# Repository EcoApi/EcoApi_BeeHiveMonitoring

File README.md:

# EcoApi Bee hive monitoring

description TBD

## Features

- External i2c sensor (ex: as6200, si7021, shtxx, ...)
- Microphone analog with max9814 (FFT with dma)
- Microphone i2s (FFT with dma)
- Weight with load scale using hx711 (opimized for 3.3V with noise filter), calibration by led information
- CPU STM32F411CEU6
- Motion detection using mercure tilt vibration sensor
- Internal i2c sensor (ex: bmp180, bme180, bme280, ...)
- Lora using rfm95w 
- Powered battery like : Li-ion, Li-po, 3xNimh, 4xNimh, LifePO4, Alkaline 3x1.5 / 2x1.5, Li-SOCL2, Li-Mn02, 18650
- Reverse battery protection
- USB charger
- Ultra low power in sleep mode (wakeup by external rtc) ~2µA
- Power in running mode TBD
- USB cdc from stm32
- Power switch for internal / external VCC (3.3V)
- Fram
- EEprom
- Flash SPI
- External nano watchdog
- Debug by led, Uart, 

## Hardware

### Characteristics

- Cpu
- Lora
- Consumption
- Fram
- EEprom
- Flash
- Rtc
- WDG
- HX711
- Protection battery
- Backup capacitor explanation
- Battery charger
- USB cdc
- Ldo
- Buck-boost
- Power Load switch
- Wakeup parts (button, wdg, motion, rtc)
- Dip switch
- Connector (load cell, external sensors, Battery, internal sensor, Debug & SWD)
- Push button
- Debug (Uart, USB CDC, SWD)
- ....

### Pcb

Front

Back

### Pinout

array of pins description

### pcb

describ options with 0R resistors. etc ...

#### JlcPcb production

- Bom and pick&place : https://support.jlcpcb.com/article/153-how-to-generate-bom-and-centroid-files-from-kicad-in-linux
- JlcPcb gerber files : https://support.jlcpcb.com/article/149-how-to-generate-gerber-and-drill-files-in-kicad

## Software

To be define (flow chart) ...

### Description

- Lora : ttn, webhook for beep, js decoder, frame format
- sensor template
- Sensors auto-detection
- Outside informations (temperature, pressure, humidity, wind, ...)
- Inside informations (Sound, temperature, humidity, gas, bee counter, custom sensor ...)
- System information (RSSI, VBATT, 
- describe directive in platforio.ini
- FFT on analog mic or I2S mic (parameters, range etc ...)
- sleep mode

### Ide & compilation

- pio
- plugins
- ....

### lmic debug ###

in platformio.ini

(1) uncomment :
	-D LMIC_DEBUG_LEVEL=2
	-D LMIC_ENABLE_event_logging=1
	-D LMIC_X_DEBUG_LEVEL=1

(2) replace in lmic/lmic.h :

#  ifdef LMIC_DEBUG_PRINTF_FN
#    define LMIC_X_DEBUG_PRINTF(f, ...) LMIC_DEBUG_PRINTF_FN(f, ## __VA_ARGS__)
#  else
#    error "LMIC_DEBUG_PRINTF_FN must be defined for LMIC_X_DEBUG_LEVEL > 0."
#  endif

by :

#define LMIC_X_DEBUG_PRINTF(f, ...) LMIC_DEBUG_PRINTF(f, ## __VA_ARGS__)

## how to

- Scale full or half
- Tare button
- Led information
- Motion tilt
- Debug
- usb charger leds
- Sleep on VBATT or 3.3V with slide switch
- Dip switch
- USB with android application (flutter.io or other)

## other 
[Editor.md](https://pandao.github.io/editor.md/en.html "Editor.md")

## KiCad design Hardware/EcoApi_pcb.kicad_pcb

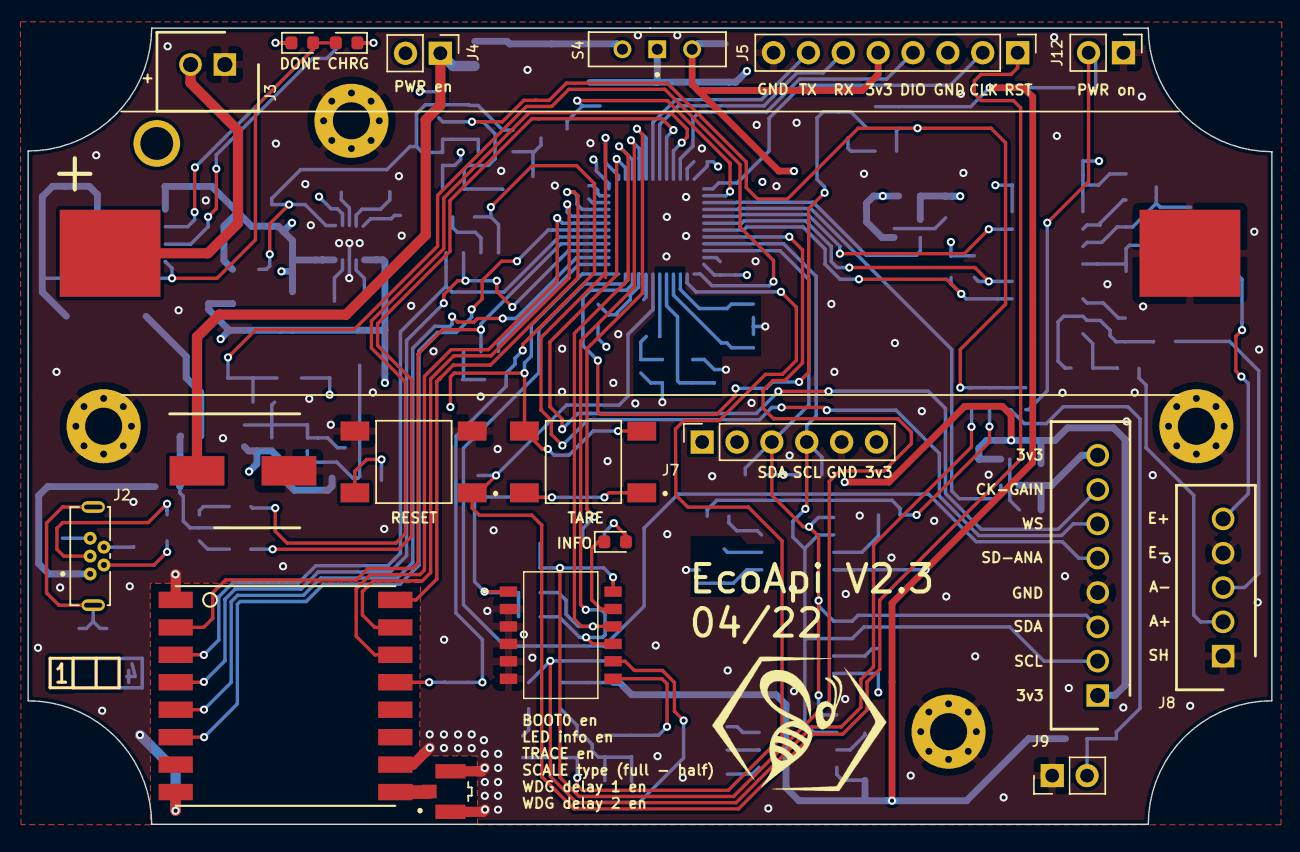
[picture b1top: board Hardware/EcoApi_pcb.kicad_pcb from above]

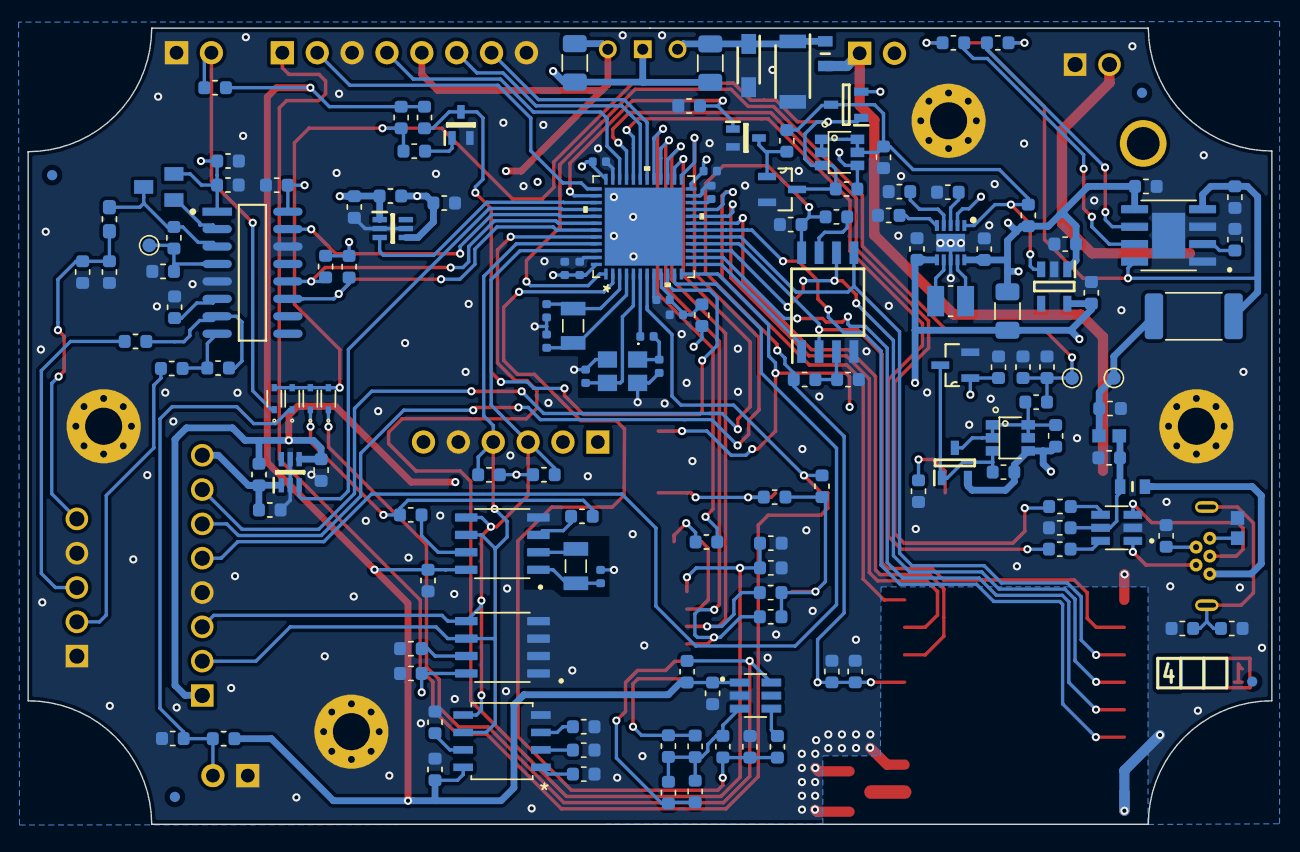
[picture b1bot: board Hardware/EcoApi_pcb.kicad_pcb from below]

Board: 4 copper layers, 90.6 x 58.0 mm, 174 parts (149 on the bottom side), 109 nets.

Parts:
BT1: 18650_HOLDER; BAT_1042
C1: 22pF; C_0402_1005Metric
C2, C5, C6, C7, C8, C10, C11, C13, C14, C15, C22, C25, C29, C30, C31, C32, C44: 0.1uF; C_0603_1608Metric
C4, C9, C12, C16, C21, C23: 10uF; C_0603_1608Metric
C17, C20: 4.7uF; C_0603_1608Metric
C18: 1000uF; CAPAE830X1050N
C19, C46: 10nF; C_0603_1608Metric
C24: 22uF; C_0603_1608Metric
C26, C27, C28, C45: 1uF; C_0603_1608Metric
C33, C34: 6pF; C_0402_1005Metric
C35, C36: 8pF; C_0402_1005Metric
C37: 1uF; C_0402_1005Metric
C38, C41, C42, C43: 0.1uF; C_0402_1005Metric
C39, C40: 4.7uF; C_0402_1005Metric
D1: RED; LED_0603_1608Metric
D2: GREEN; LED_0603_1608Metric
D3, D4, D5, D6: 1N4148WT; SODFL1608X70N
D7: BLUE; LED_0603_1608Metric
D8: USBLC6-2SC6; SOT95P280X145-6N
D9: PMEG10010ELRX; SOD123_Generic(W_F_FL)
D10: PMEG10020AELPX; SODFL4725X110N
F1, F2: MF-FSMF050X-2; FUSC1608X100N
FB1, FB2: BLM18PG221SN1D; BEADC1608X95N
H1, H2, H3, H5: MountingHole_Pad; MountingHole_2.7mm_M2.5_Pad_Via
IC1: PCF8563T_5,518; SOIC127P600X175-8N
IC2, IC3: SIP32431DR3-T1GE3; SOT65P210X110-6N
J1: UFL; IPEX_20279-001E-01
J2: 614105150721; WURTH_614105150721
J3: B2B-XH-A; SHDR2W64P0X250_1X2_740X575X700P
J4, J12: POWER ON; PinHeader_1x02_P2.54mm_Vertical
J5: Debug; PinHeader_1x08_P2.54mm_Vertical
J7: I2C INTERNAL; PinSocket_1x06_P2.54mm_Vertical
J8: B5B-XH-A__LF__SN_; SHDR5W64P0X250_1X5_1490X575X700P
J9: B8B-XH-A_LF__SN_; SHDR8W64P0X250_1X8_2240X575X700P
J10: TILT; PinHeader_1x02_P2.54mm_Vertical
L1: 3.3uH; L_0603_1608Metric_Pad1.05x0.95mm_HandSolder
L2: 2.2uH; INDC2520X120N
L3: 600Ω@100MHz; L_0603_1608Metric
LayerIcon04: VAL**; LayerNumber_4
PS1: NCP161ASN330T1G; SOT95P280X145-5N
Q1: MMBT4403; SOT23-BEC
Q2, Q7: FDC638P; SSOT-6
Q3, Q6: IRLML6244TRPBF; SOT95P237X112-3N
Q4, Q5: BSS138; SOT65P210X110-3N
Q8, Q9: BSS84AK,215; SOT95P230X110-3N
R1, R7, R8, R11, R12, R13, R17, R18, R19, R20, R24, R25, R27, R30, R31, R33, R49, R54, R55, R63: 0R; R_0603_1608Metric
R2: 182K; R_0603_1608Metric
R3: 187K; R_0603_1608Metric
R4, R5: 100R; R_0603_1608Metric
R6: 221K; R_0603_1608Metric
R9: 287K; R_0603_1608Metric
R10, R46, R56: 0R; R_1206_3216Metric
R15, R34, R42, R45, R47, R48, R51, R53, R65: 1M; R_0603_1608Metric
R16, R39, R58, R67, R68, R69, R71, R73: 10K; R_0603_1608Metric
R21: 22K; R_0603_1608Metric
R22: 20K; R_0603_1608Metric
R23, R38, R44, R50: 100K; R_0603_1608Metric
R26, R28, R29, R32: 4.7K; R_0603_1608Metric
R35: 0.5R; R_2512_6332Metric
R36, R37, R72: 1K; R_0603_1608Metric
R40, R41: 22R; R_0603_1608Metric
R52: 36.5K; R_0603_1608Metric
R75: 787R; R_0402_1005Metric
S1: TARE; SW_PUSH
S2: DSHP06TSGET
S3: RESET; SW_PUSH
S4: MSS-102559-14A-D; SW_MSS-102559-14A-D
TP3, TP4, TP20: TestPoint; TestPoint_Pad_D1.0mm
U1: TPL5010DDCR; SOT95P280X110-6N
U2: HX711; Avia_Semiconductor-HX711-IPC_A
U4: MB85RC04VPNF-G-JNERE1; MB85RC16PNF-G-JNE1
U5: RFM95W-868S2; RFM95W
U6: W25Q32JVSS; SOIC127P790X216-8N
U7: 24LC02BT-I/SN; SOIC127P600X175-8N
U8: TP4056X; SOP127P600X175-9N
U10: TPS63900DSKR; SON50P250X250X80-11N-D
U13: STM32F411CEU6
Y1: 32.768kHz 12.5pF; XTAL_ABS07-120-32.768KHZ-T
Y2: 32.768kHz 6pF; XTAL_ABS07-120-32.768KHZ-T
Y3: 25mHz 9pF +-10ppm; X322525MMB4SI

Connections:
+3V3: C24.1, C26.1, C28.1, C40.2, C41.2, C42.2, C43.2, C45.1, IC2.4, IC3.4, J5.5, J9.1, L3.1, PS1.5, R10.2, R12.1, R13.1, R26.1, R28.1, R56.1, R63.1, R68.1, R69.1, R71.1, S2.1, S4.3, U10.6, U13.24, U13.36, U13.48
+3V3_EXT: C44.1, IC3.1, J9.8, R13.2
+3V3_int: C8.1, C9.1, C10.1, C11.1, C12.1, C14.2, C15.2, C29.1, IC2.1, J7.6, Q1.E, R12.2, R29.1, R30.2, R32.1, R33.2, U2.1, U2.16, U5.13, U6.8, U7.8
+5V: C20.1, FB2.2, R35.2, TP20.1
ANA_VBATT: C46.1, R42.2, R45.1, TP3.1, U13.1
BOOT0: C31.1, R67.2, S2.12, U13.44
BTN_PWR: D3.C, J12.2, R73.2
EN_3V3: PS1.3, Q2.1, Q2.2, Q2.5, Q2.6, Q8.3, R11.1, R48.1, R53.1, U10.1
EN_3V3_EXT: IC3.3, U13.40
EN_3V3_INT: IC2.3, U13.39
EN_AVBATT-BTN_TARE: Q6.1, R23.1, S1.3, S1.4, U13.12
FLASH_NSS: U6.1, U13.13
GND: BT1.-, C1.2, C2.2, C4.2, C5.2, C7.2, C8.2, C9.2, C10.2, C11.2, C12.2, C13.1, C14.1, C15.1, C16.2, C17.2, C18.2, C19.2, C20.2, C21.2, C22.2, C23.2, C24.2, C25.2, C26.2, C27.2, C28.2, C29.2, C30.2, C31.2, C32.2, C33.2, C34.2, C35.2, C36.2, C37.1, C38.1, C39.1, C40.1, C41.1, C42.1, C43.1, C44.2, C45.2, C46.2, D8.2, D9.2, D10.2, FB1.2, H1.1, H2.1, H3.1, H5.1, IC1.4, IC2.2, IC2.5, IC3.2, IC3.5, J1.2, J1.3, J3.1, J5.3, J5.8, J7.5, J8.1, J8.4, J9.4, J10.1, J12.1, PS1.2, Q3.2, Q4.2, Q5.2, Q6.2, R16.2, R18.1, R19.1, R20.1, R22.2, R23.2, R24.1, R27.1, R31.1, R34.2, R38.2, R39.1, R45.2, R50.2, R52.2, R53.2, R54.2, R55.2, R67.1, S2.2, S2.3, S2.4, S2.5, S2.6, S3.3, S3.4, U1.2, U2.5, U2.14, U4.4, U5.1, U5.8, U5.10, U6.4, U7.1, U7.2, U7.3, U7.4, U8.1, U8.3, U8.9, U10.8, U10.11, U13.8, U13.23, U13.35, U13.47, U13.49, Y3.2, Y3.4
HX711_CK: R32.2, U2.11, U13.43
HX711_DT: R29.2, U2.12, U13.42
HX711_RATE: U2.15, U13.41
I2C1_SCL: IC1.6, J7.4, J9.2, R28.2, U4.6, U7.6, U13.45
I2C1_SDA: IC1.5, J7.3, J9.3, R26.2, U4.5, U7.5, U13.46
I2S_CK-MIC_GAIN: J9.7, U13.26
I2S_SD-MIC_ANA: J9.5, U13.11
I2S_WS: J9.6, U13.25
LED_INFO: R72.2, U13.29
LOADCELL_A+: J8.2, R5.1
LOADCELL_A-: J8.3, R4.1
LOADCELL_E+: C4.1, C5.1, J8.5, L1.1
LORA_DIO0: U5.14, U13.19
LORA_DIO1: U5.15, U13.20
LORA_DIO2: U5.16, U13.21
LORA_NSS: U5.5, U13.14
LORA_RST: U5.6, U13.18
MOTION_ALARM: C30.1, D5.C, J10.2, R65.2
NRST: C32.1, J5.1, R71.2, S3.1, S3.2, U13.7
unnamed: BT1.+, J3.2, J4.2
unnamed: C1.1, IC1.1, Y1.2
unnamed: C6.1, R4.2, U2.7
unnamed: C6.2, R5.2, U2.8
unnamed: C7.1, U2.6
unnamed: C16.1, D1.2, D2.2, R35.1, U8.4, U8.8
unnamed: C17.1, J2.SH1, J2.SH2, R34.1
unnamed: C18.1, F2.1, J4.1
unnamed: C33.1, U13.3, Y2.2
unnamed: C34.1, U13.4, Y2.1
unnamed: C35.1, U13.5, Y3.3
unnamed: C36.1, R75.1, Y3.1
unnamed: C39.2, U13.22
unnamed: D1.1, R36.2
unnamed: D2.1, R37.2
unnamed: D7.1, S2.11
unnamed: D7.2, R72.1
unnamed: D8.1, J2.2
unnamed: D8.3, J2.3
unnamed: D8.4, R41.1
unnamed: D8.6, R40.1
unnamed: F1.1, J2.1
unnamed: FB1.1, J2.5
unnamed: IC1.2, Y1.1
unnamed: IC1.3, R7.1
unnamed: IC1.7, R8.1
unnamed: J1.1, U5.9
unnamed: J2.4, R38.1
unnamed: L1.2, Q1.C, R21.1, U2.3
unnamed: L2.1, U10.7
unnamed: L2.2, U10.9
unnamed: Q1.B, U2.2
unnamed: Q3.1, Q4.3, R48.2
unnamed: Q5.1, R49.1
unnamed: Q6.3, Q7.3, Q9.1, R15.2
unnamed: Q7.1, Q7.2, Q7.5, Q7.6, Q9.3, R25.2, R42.1
unnamed: R1.1, R2.1, R3.1, R6.1, R9.1, U1.3
unnamed: R17.2, U1.4
unnamed: R18.2, U4.1
unnamed: R19.2, U4.2
unnamed: R20.2, U4.3
unnamed: R21.2, R22.1, TP4.1, U2.4
unnamed: R24.2, U4.7
unnamed: R27.2, U7.7
unnamed: R30.1, R31.2, U6.3
unnamed: R33.1, U6.7
unnamed: R36.1, U8.7
unnamed: R37.1, U8.6
unnamed: R39.2, U8.2
unnamed: R52.1, U10.3
unnamed: R54.1, U10.4
unnamed: R55.1, U10.5
unnamed: R63.2, S1.1, S1.2
unnamed: R75.2, U13.6
PWR_OFF: Q4.1, R50.1, U13.38
PWR_ON: D3.A, D4.A, D5.A, D6.A, Q2.3, Q3.3, Q8.1, R44.2, R47.2, R49.2
RTC_ALARM: D4.C, R7.2, R8.2
SCALE_TYPE: R69.2, S2.9, U13.28
SPI1_MISO: U5.2, U6.2, U13.16
SPI1_MOSI: U5.3, U6.5, U13.17
SPI1_SCK: U5.4, U6.6, U13.15
SW_CLK: J5.2, U13.37
SW_DIO: J5.4, U13.34
TRACE_EN: R68.2, S2.10, U13.27
UART_RX: J5.6, U13.31
UART_TX: J5.7, U13.30
USB_DN: R40.2, U13.32
USB_DP: R41.2, U13.33
VBATT: C21.1, C23.1, C27.1, D9.1, D10.1, F2.2, PS1.1, Q2.4, Q7.4, Q8.2, Q9.2, R10.1, R11.2, R15.1, R25.1, R44.1, R46.1, S4.2, U8.5, U10.2, U10.10
VBUS: C19.1, C22.1, D8.5, F1.2, FB2.1
VREF+: C37.2, C38.2, L3.2, U13.9
V_WKUP: C2.1, C13.2, C25.1, IC1.8, R46.2, R47.1, R51.1, R56.2, R58.2, R65.1, R73.1, S4.1, U1.1, U4.8
WAKEUP: Q5.3, R51.2, U13.10
WDG_ALARM: D6.C, R58.1, U1.6
WDG_DELAY1: R2.2, R3.2, S2.8
WDG_DELAY2: R6.2, R9.2, S2.7
WDG_RELOAD: R1.2, R16.1, R17.1, U13.2

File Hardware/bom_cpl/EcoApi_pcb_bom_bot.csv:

"Comment","Designator","Footprint","LCSC Part #"
"0.1uF","C8 C7 C5 C6 C10 C11 C14 C15 C13 C2 C25 C22 C29 C44 C30 C31 C32","0603","C1591"
"10uF","C9 C4 C12 C16 C21","0603","C19702"
"4.7K","R26 R28 R29 R32","0603","C23162"
"HX711","U2","SOP-16","C43656"
"100R","R4 R5","0603","C54021"
"20K","R22","0603","C4184"
"22K","R21","0603","C31850"
"3.3uH","L1","0603","C21189"
"MB85RC04VPNF-G-JNERE1","U4","SOIC-8","C8738"
"24LC02BT-I/SN","U7","SOIC-8","C5453"
"W25Q32JVSS","U6","SOP-8","C82344"
"0R","R20 R19 R18 R31 R8 R54 R55 R12 R13 R11 R25","0603","NM_C21189"
"0R","R30 R33 R27 R24 R1 R17 R7 R49 R63","0603","C21189"
"221K","R6","0603","C22894"
"287K","R9","0603","C22972"
"182K","R2","0603","C22894"
"187K","R3","0603","C22896"
"MMBT4403","Q1","SOT-23-3","C85183"
"PCF8563T_5,518","IC1","SOIC-8","C7440"
"TPL5010DDCR","U1","SOT-23-6","C473912"
"32.768kHz 12.5pF","Y1","3215","C97606"
"22pF","C1","0402","C76960"
"10K","R16 R58 R39 R68 R73 R67 R71 R69","0603","C25804"
"TPS63900DSKR","U10","",""
"10uF","C23","0603","NM_C19702"
"22uF","C24","0603","NM_C59461"
"36.5K","R52","0603","NM_C51261_"
"TP4056X","U8","SOP-8","C2763448"
"1K","R37 R36 R72","0603","C21190"
"0.5R","R35","2512","C27777"
"100K","R50 R44 R38 R23","0603","C25803"
"IRLML6244TRPBF","Q3 Q6","SOT-23-3","C143946"
"1M","R47 R48 R53 R34 R51 R65 R42 R15 R45","0603","C22935"
"10nF","C19 C46","0603","C100042"
"4.7uF","C20 C17","0603","C19666"
"22R","R40 R41","0603","C23345"
"BLM18PG221SN1D","FB2 FB1","0603","C80165"
"MF-FSMF050X-2","F1 F2","0603","C210357"
"FDC638P","Q2 Q7","SSOT-6",""
"1N4148WT","D6 D4 D5 D3","SOD-523","C232841"
"2.2uH","L2","0603",""
"SIP32431DR3-T1GE3","IC2 IC3","SC-70-6","C141606"
"BSS138","Q5 Q4","SOT-323-3","C24553"
"USBLC6-2SC6","D8","SOT-23-6","C7519"
"1uF","C26 C28 C27 C45","0603","C59782"
"0R","R10 R46 R56","1206","NM_C17888"
"NCP161ASN330T1G","PS1","SOT-23-5","C892187"
"BSS84AK,215","Q8 Q9","SOT-23-3","C127273"
"PMEG10020AELPX","D10","SOD-128","C503397"
"PMEG10010ELRX","D9","SOD-123W","C179426"
"4.7uF","C39 C40","0402","C77004"
"STM32F411CEU6","U13","UFQFPN-48","C60420"
"0.1uF","C41 C42 C43 C38","0402","C1525"
"1uF","C37","0402","C307427"
"25mHz 9pF +-10ppm","Y3","3225","C255920"
"8pF","C35 C36","0402","C161335"
"787R","R75","0402","C270582"
"32.768kHz 6pF","Y2","3215","C2692145"
"6pF","C34 C33","0402","C437443"
"600Ω@100MHz","L3","0603","C133937"

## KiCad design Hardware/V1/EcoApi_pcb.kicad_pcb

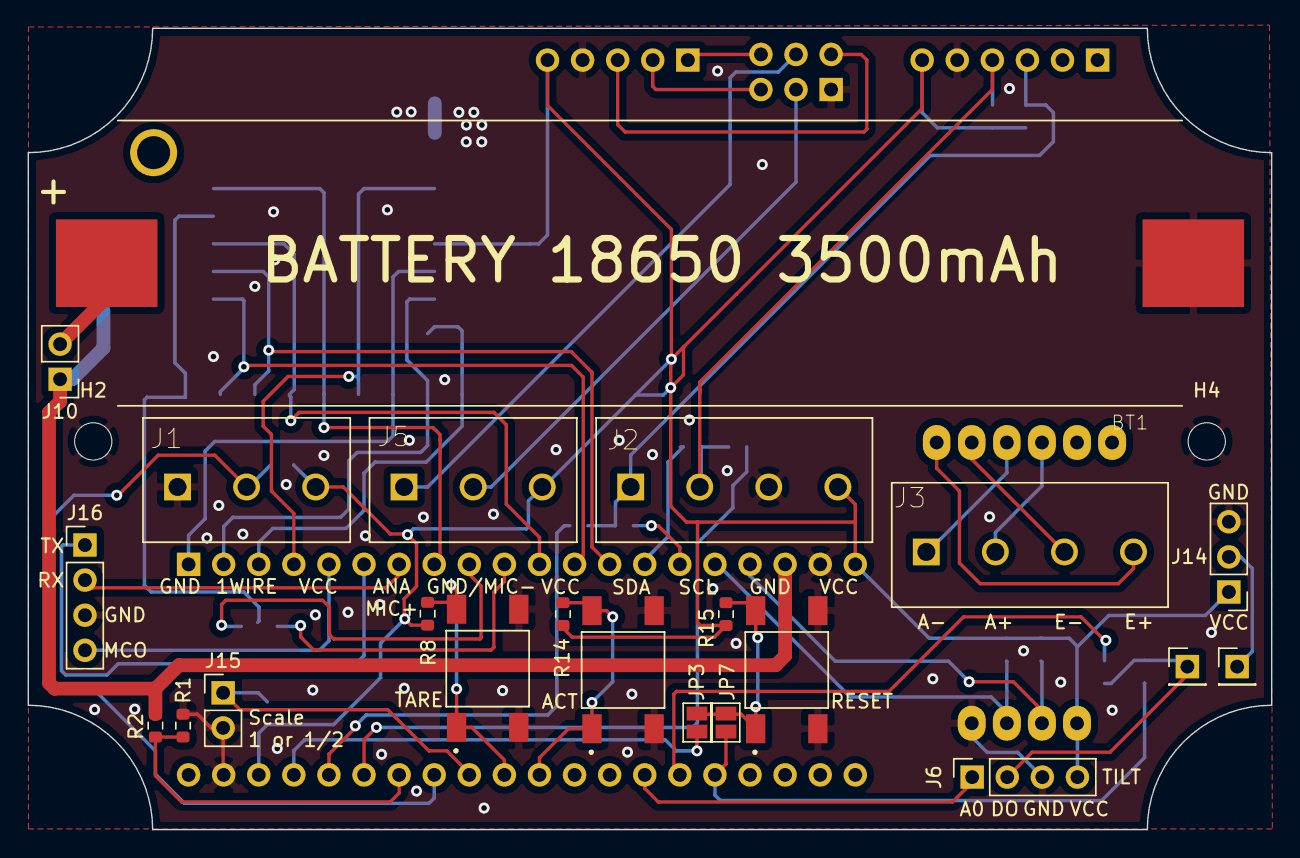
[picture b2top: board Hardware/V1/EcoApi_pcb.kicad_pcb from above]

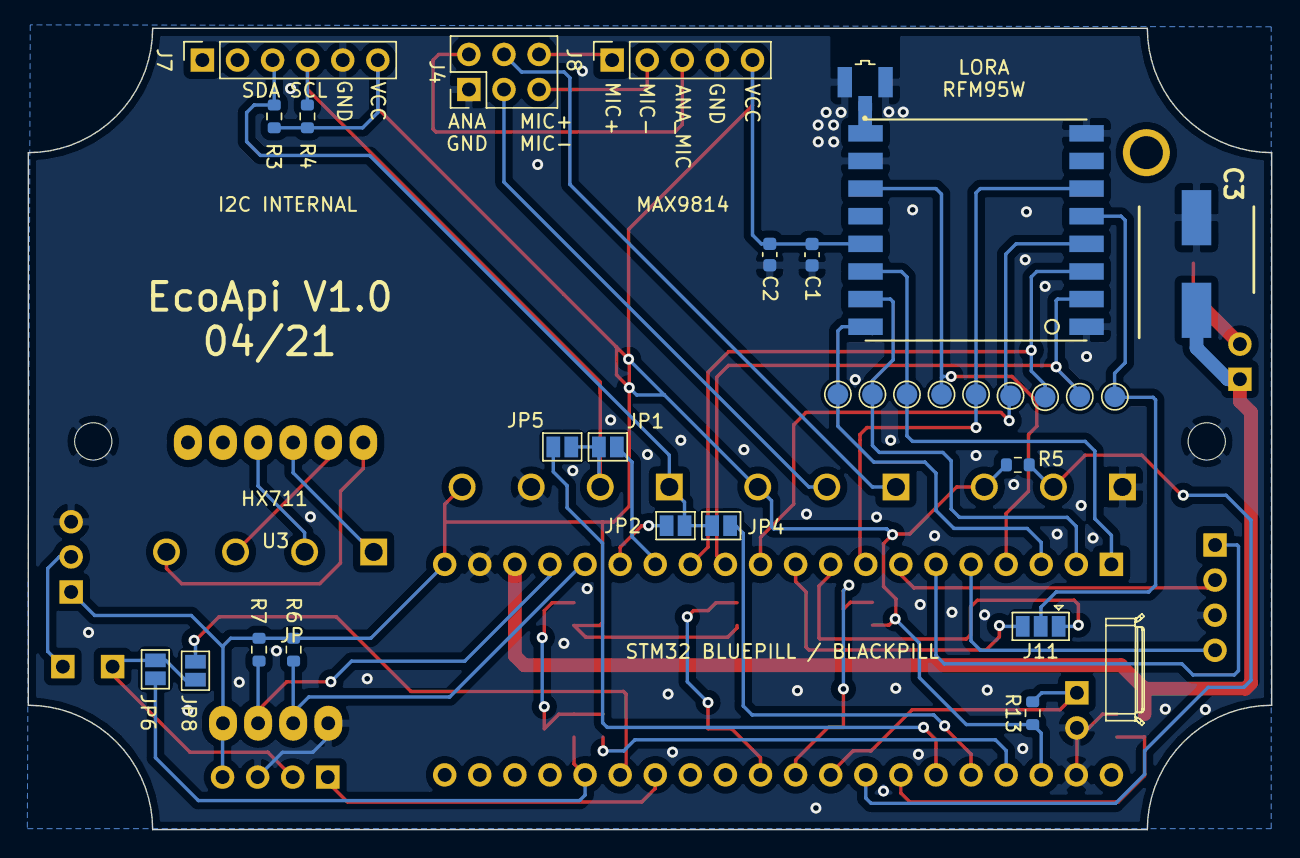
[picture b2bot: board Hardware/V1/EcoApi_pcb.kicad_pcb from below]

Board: 2 copper layers, 90.0 x 58.0 mm, 56 parts (32 on the bottom side), 48 nets.

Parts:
BT1: 18650_keystone_battery_holder; BAT_1042
C1: 100n; C_0603_1608Metric
C2: 10u; C_0603_1608Metric
C3: EEE-FK0J102GP; CAPAE830X1050N
H2, H4: MountingHole_Pad; MountingHole_2.7mm
J0: UFL; IPEX_20279-001E-01
J1: 1-WIRE; CUI_TB001-500-03BE
J2: I2C EXTERNAL; CUI_TB001-500-04BE
J3: LOAD CELL; CUI_TB001-500-04BE
J4: INT/EXT; PinHeader_2x03_P2.54mm_Vertical
J5: MAX9814 EXTERNAL; CUI_TB001-500-03BE
J6: TILT VIBRATION; PinSocket_1x04_P2.54mm_Vertical
J7: I2C INTERNAL; PinSocket_1x06_P2.54mm_Vertical
J8: MAX9814 INTERNAL; PinSocket_1x05_P2.54mm_Vertical
J10: POWER ON; PinHeader_1x02_P2.54mm_Vertical
J11: CS LORA; SolderJumper-3_P1.3mm_Open_Pad1.0x1.5mm
J12: TILT IN; PinHeader_1x01_P2.54mm_Vertical
J13: TILT_OUT; PinHeader_1x01_P2.54mm_Vertical
J14: INT/EXT; PinHeader_1x03_P2.54mm_Vertical
J15: 1/2 SCALE; PinHeader_1x02_P2.54mm_Vertical
J16: DEBUG; PinHeader_1x04_P2.54mm_Vertical
JP1, JP2, JP3, JP4, JP5, JP6, JP7, JP8: Jumper_NO_Small; SolderJumper-2_P1.3mm_Open_Pad1.0x1.5mm
R1: 330k; R_0603_1608Metric
R2: 100k; R_0603_1608Metric
R3, R4, R5, R6, R7: 4.7k; R_0603_1608Metric
R8, R13, R14, R15: 10k; R_0603_1608Metric
S1: ACTION; SW_PUSH
S2: TARE; SW_PUSH
S3: RESET; SW_PUSH
TP3, TP7, TP8, TP9, TP10, TP11, TP12, TP15, TP16: TestPoint; TestPoint_Pad_D1.5mm
U1: stm32_bluepill
U2: RFM95W-868S2; RFM95W
U3: HX711

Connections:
1WIRE_DATA: J1.2, R5.2, U1.33
+3V3: C1.1, C2.1, J1.3, J2.4, J5.3, J6.4, J7.6, J8.5, J14.1, R3.1, R4.1, R5.1, R6.1, R7.1, R8.1, R13.1, R14.1, R15.1, U1.20, U1.38, U2.13, U3.10
ANA_MIC: J4.4, J8.3
ANA_VBATT: R1.2, R2.1, U1.34
BTN_ACT: R14.2, S1.1, S1.2, U1.30
BTN_RST: JP3.2, JP7.2, R15.2, S3.1, S3.2
BTN_TARE: R8.2, S2.1, S2.2, U1.31
GND: BT1.-, C1.2, C2.2, C3.2, H2.1, H4.1, J0.2, J0.3, J1.1, J2.3, J4.1, J6.3, J7.5, J8.4, J14.3, J15.2, J16.3, R2.2, S1.3, S1.4, S2.3, S2.4, S3.3, S3.4, U1.19, U1.39, U2.1, U2.8, U2.10, U3.7
HX711_CK: R7.2, U1.17, U3.9
HX711_DT: R6.2, U1.16, U3.8
I2C1_SCL: J2.2, J7.4, JP1.1, JP5.2, R4.2
I2C1_SDA: J2.1, J7.3, JP2.1, JP4.2, R3.2
LOADCELL_A+: J3.2, U3.4
LOADCELL_A-: J3.1, U3.3
LOADCELL_E+: J3.4, U3.1
LOADCELL_E-: J3.3, U3.2
LORA_DIO0: TP11.1, U1.1, U2.14
LORA_DIO1: TP12.1, U1.2, U2.15
LORA_DIO2: TP15.1, U1.3, U2.16
LORA_DIO3: TP16.1, U1.4, U2.11
LORA_NSS: J11.1, U1.9
LORA_RST: TP10.1, U1.8, U2.6
MCO: J16.4, U1.5
MIC+: J4.6, J8.1
MIC-: J4.3, J8.2
unnamed: BT1.+, J10.2
unnamed: J0.1, U2.9
unnamed: J11.2, TP3.1, U2.5
unnamed: J13.1, J14.2
unnamed: JP1.2, U1.14
unnamed: JP2.2, U1.15
unnamed: JP3.1, U1.37
unnamed: JP4.1, U1.36
unnamed: JP5.1, U1.35
unnamed: JP6.1, JP7.1, U1.25
unnamed: JP8.1, U1.26
RING: J6.2, J12.1, JP6.2, JP8.2
RING_ANA: J6.1, U1.27
SCALE_TYPE: J15.1, R13.2, U1.32
SOUND1: J4.2, J5.2
SOUND2: J4.5, J5.1
SPI1_MISO: TP9.1, U1.12, U2.2
SPI1_MOSI: TP8.1, U1.13, U2.3
SPI1_NSS: J11.3, U1.10
SPI1_SCK: TP7.1, U1.11, U2.4
UART1_RX: J16.2, U1.7
UART1_TX: J16.1, U1.6
VCC: C3.1, J10.1, R1.1, U1.18

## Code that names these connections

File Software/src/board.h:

/************************************************************************************//**
 *
 *	\file		board.h
 *
 *	\brief
 *
 *	\date		2 nov. 2021
 *
 *	\author		ecoapi
 *
 ***************************************************************************************/

#ifndef __BOARD_H_
#define __BOARD_H_

/***************************************************************************************/
/*	Includes																		
/***************************************************************************************/
#include <Arduino.h>

#ifdef __cplusplus
extern "C" {
#endif

#if defined(STM32F411xE) //blackpill
    #include "stm32f4xx_hal_rcc.h"
    #include "stm32f4xx_hal_adc.h"
    //#include "stm32f4xx_ll_adc.h"
#elif defined(STM32F103xB) //bluepill 
    #include "stm32f1xx_hal_rcc.h"
    #include "stm32f1xx_hal_adc.h"
    //#include "stm32f1xx_ll_adc.h"
#else
    #error "Bad µC defined"
#endif

#include "stm32yyxx_ll_adc.h"

/***************************************************************************************/
/* Define
/***************************************************************************************/
#define PACK( __Declaration__ ) __Declaration__ __attribute__((__packed__))

/*
-O0 : optimize for compile time and debug-ability. Most performance optimizations are disabled. This is the default for GCC.
-O1: pick the low hanging fruit in terms of performance, without impacting compilation time too much.
-O2: optimize for performance more aggressively, but not at the cost of larger code size.
-O3: optimize for performance at all cost, no matter the code size or compilation time impact.
-Ofast a.k.a. ludicrous mode: take off the guard rails, and disregard strict C standard compliance in the name of speed. This may lead to invalid programs.
-Os optimize for code size. This uses O2 as the baseline, but disables some optimizations. For example, it will not inline3 code if that leads to a size increase.

or

#pragma GCC push_options
#pragma GCC optimize ("O3")

 Code that needs optimizing

#pragma GCC pop_options
*/

//#define WEAK __attribute__ ((weak))

#define TRUE (1)
#define FALSE !(TRUE)

#define OK (0)
#define ERROR (-1)
#define DATA_NOT_CHANGED (ERROR - 1)

#define HX711_RATE PB5
#define HX711_DT PB6
#define HX711_CK PB7

#define SPI1_MOSI PA7
#define SPI1_MISO PA6
#define SPI1_SCK PA5
//#define SPI1_NSS PA_15
#define FLASH_NSS PA3
#define LORA_NSS PA4
#define LORA_RST PB0
#define LORA_DIO0 PB1
#define LORA_DIO1 PB2
#define LORA_DIO2 PB10
//#define LORA_DIO3 30//PB_15

#define UART1_TX PA9
#define UART1_RX PA10

#define PWR_OFF PA15

#define LED_INFO PA8
#define LED_BUITIN LED_INFO


#define WAKEUP_PIN PWR_WAKEUP_PIN1
#define WAKEUP PA0

//#define BTN_RST ?
//#define ONEWIRE_DATA PA_7
//#define ANA_VBATT PB_0
#define SCALE_TYPE PB15

#define BTN_TARE PA2
#define EN_VBATT BTN_TARE

#define TRACE_EN PB14
//#define BTN_ACT PA_4
//#define RING PA_1 //SYS_WKUP1

#define WDG_RELOAD PC13

#define MIC_ANA PA1
#define MIC_GAIN PB13

#define I2S_SD MIC_ANA
#define I2S_CK MIC_GAIN
#define I2S_WS PB12

#define I2C1_SCL PB8
#define I2C1_SDA PB9


#define EN_3V3_INT PB3
#define EN_3V3_EXT PB4

#ifdef __cplusplus
}
#endif
#endif

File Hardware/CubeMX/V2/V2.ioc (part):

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Mcu.Name=STM32F411C(C-E)Ux
Mcu.Package=UFQFPN48
Mcu.UserName=STM32F411CEUx
PA0-WKUP.GPIOParameters=GPIO_Label
PA0-WKUP.GPIO_Label=WAKEUP
PA0-WKUP.Mode=SYS_WakeUp0
PA0-WKUP.Signal=SYS_WKUP
PA1.GPIOParameters=GPIO_Label
PA1.GPIO_Label=I2S_SD/MIC_ANA
PA1.Mode=Half_Duplex_Master
PA1.Signal=I2S4_SD
PA10.Mode=Asynchronous
PA10.Signal=USART1_RX
PA11.GPIOParameters=GPIO_Label
PA11.GPIO_Label=USB_DN
PA11.Mode=Device_Only
PA11.Signal=USB_OTG_FS_DM
PA12.GPIOParameters=GPIO_Label
PA12.GPIO_Label=USB_DP
PA12.Mode=Device_Only
PA12.Signal=USB_OTG_FS_DP
PA13.GPIOParameters=GPIO_Label
PA13.GPIO_Label=SW_DIO
PA13.Mode=Serial_Wire
PA13.Signal=SYS_JTMS-SWDIO
PA14.GPIOParameters=GPIO_Label
PA14.GPIO_Label=SW_CLK
PA14.Mode=Serial_Wire
PA14.Signal=SYS_JTCK-SWCLK
PA15.GPIOParameters=GPIO_Label
PA15.GPIO_Label=PWR_OFF
PA15.Signal=GPIO_Output
PA2.GPIOParameters=GPIO_Label
PA2.GPIO_Label=BTN_TARE/EN_AVBATT 
PA2.Signal=GPIO_Input
PA3.GPIOParameters=GPIO_Label
PA3.GPIO_Label=FLASH_NSS
PA3.Signal=GPIO_Output
PA4.GPIOParameters=GPIO_Label
PA4.GPIO_Label=LORA_NSS
PA4.Mode=NSS_Signal_Hard_Output
PA4.Signal=SPI1_NSS
PA5.Mode=Full_Duplex_Master
PA5.Signal=SPI1_SCK
PA6.Mode=Full_Duplex_Master
PA6.Signal=SPI1_MISO
PA7.Mode=Full_Duplex_Master
PA7.Signal=SPI1_MOSI
PA8.GPIOParameters=GPIO_Label
PA8.GPIO_Label=MCO/LED_INFO
PA8.Mode=Clock-out-1
PA8.Signal=RCC_MCO_1
PA9.Mode=Asynchronous
PA9.Signal=USART1_TX
PB0.GPIOParameters=GPIO_Label
PB0.GPIO_Label=LORA_RST
PB0.Signal=GPIO_Output
PB1.GPIOParameters=GPIO_Label
PB1.GPIO_Label=LORA_DIO0
PB1.Signal=GPIO_Input
PB10.GPIOParameters=GPIO_Label
PB10.GPIO_Label=LORA_DIO2
PB10.Signal=GPIO_Input
PB12.GPIOParameters=GPIO_Label
PB12.GPIO_Label=I2S_WS
PB12.Mode=Half_Duplex_Master
PB12.Signal=I2S4_WS
PB13.GPIOParameters=GPIO_Label
PB13.GPIO_Label=I2S_CK/MIC_GAIN
PB13.Mode=Half_Duplex_Master
PB13.Signal=I2S4_CK
PB14.GPIOParameters=GPIO_Label
PB14.GPIO_Label=TRACE_EN
PB14.Signal=GPIO_Input
PB15.GPIOParameters=GPIO_Label
PB15.GPIO_Label=SCALE_TYPE
PB15.Signal=GPIO_Input
PB2.GPIOParameters=GPIO_Label
PB2.GPIO_Label=LORA_DIO1
PB2.Signal=GPIO_Input
PB3.GPIOParameters=GPIO_Label
PB3.GPIO_Label=EN_3V3_INT
PB3.Signal=GPIO_Output
PB4.GPIOParameters=GPIO_Label
PB4.GPIO_Label=EN_3V3_EXT
PB4.Signal=GPIO_Output
PB5.GPIOParameters=GPIO_Label
PB5.GPIO_Label=HX711_RATE
PB5.Signal=GPIO_Output
PB6.GPIOParameters=GPIO_Label
PB6.GPIO_Label=HX711_DT
PB6.Signal=GPIO_Input
PB7.GPIOParameters=GPIO_Label
PB7.GPIO_Label=HX711_CK
PB7.Signal=GPIO_Output
PB8.Mode=I2C
PB8.Signal=I2C1_SCL
PB9.Mode=I2C
PB9.Signal=I2C1_SDA
PC13-ANTI_TAMP.GPIOParameters=GPIO_Label
PC13-ANTI_TAMP.GPIO_Label=WDG_RELOAD
PC13-ANTI_TAMP.Signal=GPIO_Output
PC14-OSC32_IN.Mode=LSE-External-Oscillator
PC14-OSC32_IN.Signal=RCC_OSC32_IN
PC15-OSC32_OUT.Mode=LSE-External-Oscillator
PC15-OSC32_OUT.Signal=RCC_OSC32_OUT
PH0\ -\ OSC_IN.Mode=HSE-External-Oscillator
PH0\ -\ OSC_IN.Signal=RCC_OSC_IN
PH1\ -\ OSC_OUT.Mode=HSE-External-Oscillator
PH1\ -\ OSC_OUT.Signal=RCC_OSC_OUT
RCC.HSE_VALUE=25000000
RCC.SYSCLKFreq_VALUE=16000000
board=custom

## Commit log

2021-04-09 Add V1.0 hardware files (kicad project)
2021-04-09 Add pdf schematic
2021-04-09 Add first readme
2021-04-09 Add files via upload
    Add hx711 datasheet
2021-04-09 Add files via upload
    Add datasheets
2021-10-29 Add lora, adc, bmp180, trace, 1wire and hx711
2021-10-29 update gitignore
2021-10-29 Move platformio.ini
2021-11-02 Optimize tree file
2021-11-02 Fix illegall access and add wdg
2021-11-05 Fix power consumption 120µA for the moment (regulator on blackpill board)
2021-11-07 Optimize consumption
2021-12-03 Add fft from audio ana mic (max9814) and add sht3x sensor and add dwonlink adr support
2021-12-03 Change platformio.ini
2021-12-04 Remove fft outpu noise
2021-12-06 Change default setting for audio
2022-01-07 Add V2 schematic
2022-01-07 Remove V1 Hardware info
2022-01-26 Add pcb route and ground plane
2022-02-16 Fix drc error
2022-02-17 Add text on pcb front side
2022-03-09 Update pcb to v2.1 (Add ldo)
2022-03-24 Add Gerber files, Bom, Jlcpcb LCSC parts ref, some optimizations
2022-04-01 Fix JLCPCB assembly issues, Add reverse battery protection, Define Correct crystal capa, Add Layer number and fiducial, and some quicq fix
2022-04-01 Add bom compatible with JLCPCB SMT assembly (LCSC refs), Add pick and place file with components rotation fixed
2022-04-01 Update README.md
    Add link to JlcPcb tips for kicad
2022-04-01 Update images
2022-04-01 Add pinout image, Update stmCubeMx project
2023-01-29 Debug some features on hardware
2023-01-30 Fix motion detection, validation done for usb solar charger
2023-02-15 Fix rtc write time, fix hx711 rate, Add offset for vbatt, start i2s dma mic
2023-03-01 Fix i2s and usb cdc
2023-03-02 Filter low frequency for I2S mic and scale fft result to u16
2023-03-03 Add mic auto-detect, add low cut frequency for i2s, add waiting time for vbatt read
2023-03-19 Fix rtc alarm lock 23:59 -> 00:xx, saturday to sunday
2023-03-25 Add eeprom usage for fixed settings

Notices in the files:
parts and their libraries:
Copyright 2021 Accelerated Designs. All rights reserved.
